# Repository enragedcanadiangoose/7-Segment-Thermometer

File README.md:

# 7-Segment-Thermometer
A simple project using two thermal sensors (DS18B20) an arduino nano and a four digit common cathode seven-segment display

<!-- TABLE OF CONTENTS -->
<details>
  <summary>Table of Contents</summary>
  <ol>
    <li>
      <a href="#about-the-project">About The Project</a>
    </li>
    <li>
      <a href="#getting-started">Getting Started</a>
      <ul>
        <li><a href="#Prerequisites">Prerequisites</a></li>
        <li><a href="#Installation">Installation</a></li>
        <li><a href="#building-the-circuit">Building the circuit</a></li>
        <li><a href="#how-it-works">How It Works</a></li>
      </ul>
    </li>
    <li><a href="#roadmap">Roadmap</a></li>
    <li><a href="#contact">Contact</a></li>
        <li><a href="#license">License</a></li>
  </ol>
</details>

## About The Project
This is a simple project created using an Arduino Nano paired with two thermal sensors (DS18B20 or compatible) and a seven-segment display used to show the temperature both inside and outside of my room. 
<p align="right">(<a href="#readme-top">back to top</a>)</p>

<!-- GETTING STARTED -->
## Getting Started

Replicating the project

### Prerequisites

* Arduino IDE
    * install from the Arduino library manager
        * OneWire.h
        * DallasTemperature.h

### Installation

1. Clone the repo
```sh
git clone https://github.com/enragedcanadiangoose/7-Segment-Thermometer.git
```
2. Open the "./7-Segment-Thermometer/Thermometer/" folder in the Arduino IDE

### Building The Circuit

<p>You can follow this diagram to replicate the circuit I used, this should let the code function with no modification</p>
  
<p>Here is the version that I built on a prototyping breadboard, it's a bit of a sloppy prototype but it works</p>

### How It Works

* The Arduino polls the active thermal sensor every 30s for up to keep the data being displayed up to date
    * The display will blank during this time since the Arduino can't draw the display and poll the sensors simultaneously
* The desired thermal sensor is selected using the toggle switch
* The presence of the decimal point indicates if the temperature is positive or negative
    * on = ≥ 0
    * off = ≤ 0
<p align="right">(<a href="#readme-top">back to top</a>)</p>

## Roadmap

<p>At some point a run of PCBs may be manufactured</p>
<p align="right">(<a href="#readme-top">back to top</a>)</p>

## Contact
<p>email: astew2693@gmail.com</p>
<p align="right">(<a href="#readme-top">back to top</a>)</p>

## License

<p>see <a href="https://github.com/enragedcanadiangoose/7-Segment-Thermometer/blob/main/LICENSE">LICENSE</a> for details</p>

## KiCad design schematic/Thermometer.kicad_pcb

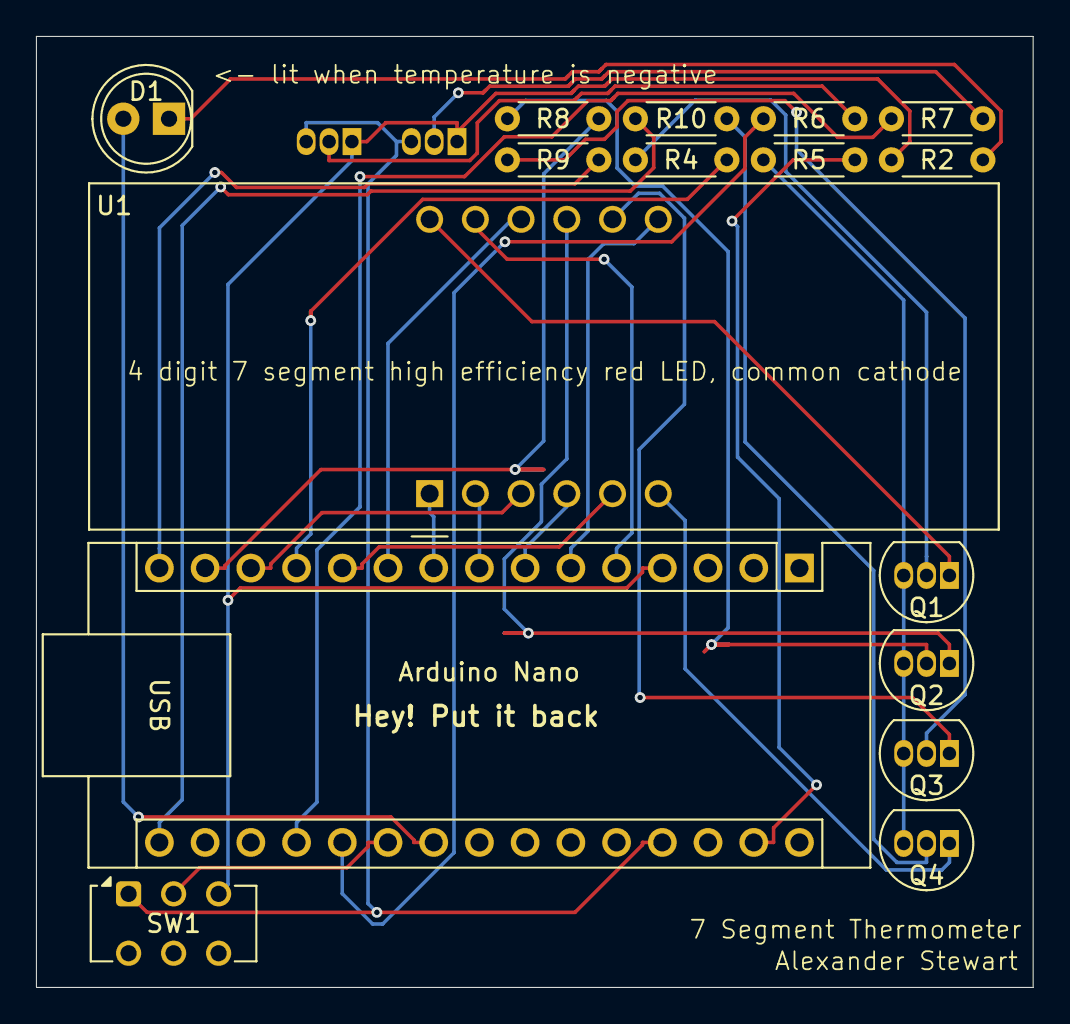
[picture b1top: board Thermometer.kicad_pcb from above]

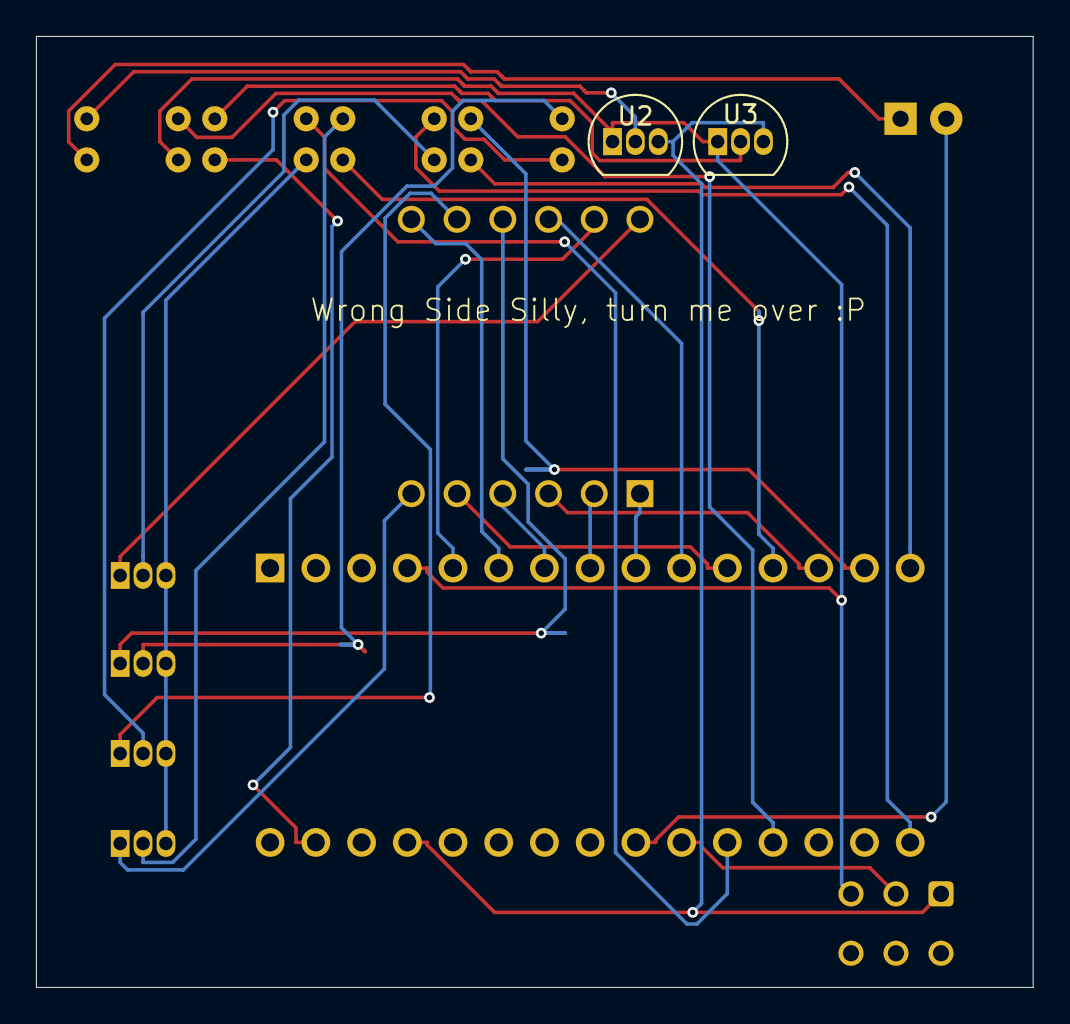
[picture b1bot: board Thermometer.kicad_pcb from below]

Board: 2 copper layers, 55.4 x 52.8 mm, 18 parts (2 on the bottom side), 31 nets.

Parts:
Arduino Nano: Arduino_Nano_v2.x; Arduino_Nano
D1: LED; LED_D5.0mm
Q1, Q2, Q3, Q4: BC547; TO-92_Inline
R2: 220; R_Axial_DIN0204_L3.6mm_D1.6mm_P5.08mm_Horizontal
R4, R8, R9, R10: 100k; R_Axial_DIN0204_L3.6mm_D1.6mm_P5.08mm_Horizontal
R5: 550; R_Axial_DIN0204_L3.6mm_D1.6mm_P5.08mm_Horizontal
R6, R7: 4.7k; R_Axial_DIN0204_L3.6mm_D1.6mm_P5.08mm_Horizontal
SW1: SW_SPDT; SW_CK_JS202011CQN_DPDT_Straight
U1: CC56-12EWA; CA56-12EWA
U2, U3: DS18B20; TO-92_Inline

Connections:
unnamed: Arduino Nano.27 (+5V), SW1.1 (A), U2.3 (V_{DD}), U3.3 (V_{DD})
unnamed: Arduino Nano.19 (A0), R7.2
unnamed: Arduino Nano.20 (A1), R6.2
unnamed: Arduino Nano.21 (A2), SW1.2 (B)
unnamed: Arduino Nano.22 (A3), D1.2 (A)
unnamed: Arduino Nano.5 (D2), U1.11 (a)
unnamed: Arduino Nano.6 (D3), U1.7 (b)
unnamed: Arduino Nano.7 (D4), U1.4 (c)
unnamed: Arduino Nano.8 (D5), U1.2 (d)
unnamed: Arduino Nano.9 (D6), U1.1 (e)
unnamed: Arduino Nano.10 (D7), U1.10 (f)
unnamed: Arduino Nano.11 (D8), U1.5 (g)
unnamed: Arduino Nano.12 (D9), R4.1
unnamed: Arduino Nano.13 (D10), U1.3 (DPX)
unnamed: Arduino Nano.14 (D11), R8.1
unnamed: Arduino Nano.15 (D12), R9.1
unnamed: Arduino Nano.16 (D13), R10.1
unnamed: Arduino Nano.29 (GND), R5.1
unnamed: D1.1 (K), R2.1
unnamed: Q1.2 (B), R4.2
unnamed: Q1.1 (C), U1.12 (CC1)
unnamed: Q1.3 (E), Q2.3 (E), Q3.3 (E), Q4.3 (E), R5.2
unnamed: Q2.2 (B), R8.2
unnamed: Q2.1 (C), U1.9 (CC2)
unnamed: Q3.2 (B), R9.2
unnamed: Q3.1 (C), U1.8 (CC3)
unnamed: Q4.2 (B), R10.2
unnamed: Q4.1 (C), U1.6 (CC4)
unnamed: Arduino Nano.4 (GND), R2.2, SW1.3 (C), U2.1 (GND), U3.1 (GND)
unnamed: R7.1, U2.2 (DQ)
unnamed: R6.1, U3.2 (DQ)

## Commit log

2025-03-30 adding the code
    adding the code for the display
2025-03-30 Schematic Diagram added
    added a schematic diagram of the circuit
2025-03-30 Update README.md
    added a proper readme
2025-09-09 Updated Readme Formatting and Schematic Comments
2025-09-11 Optimized the display drawing routines and added optional serial temperature outputs
2025-09-16 Updated the Character matrix to fix some broken characters
2025-09-16 Updated Schematic
2025-09-23 Created a PCB design for the board
2025-11-04 Updated Schematic and PCB with (hopefully) final designs
2026-01-16 updated code formatting
2026-01-16 Updated error in PCB design
2026-04-23 fixed code formatting
2026-04-23 added printing of temps to the serial port
